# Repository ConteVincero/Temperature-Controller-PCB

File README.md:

# Temperature-Controller
PCB to control the temperature in the house

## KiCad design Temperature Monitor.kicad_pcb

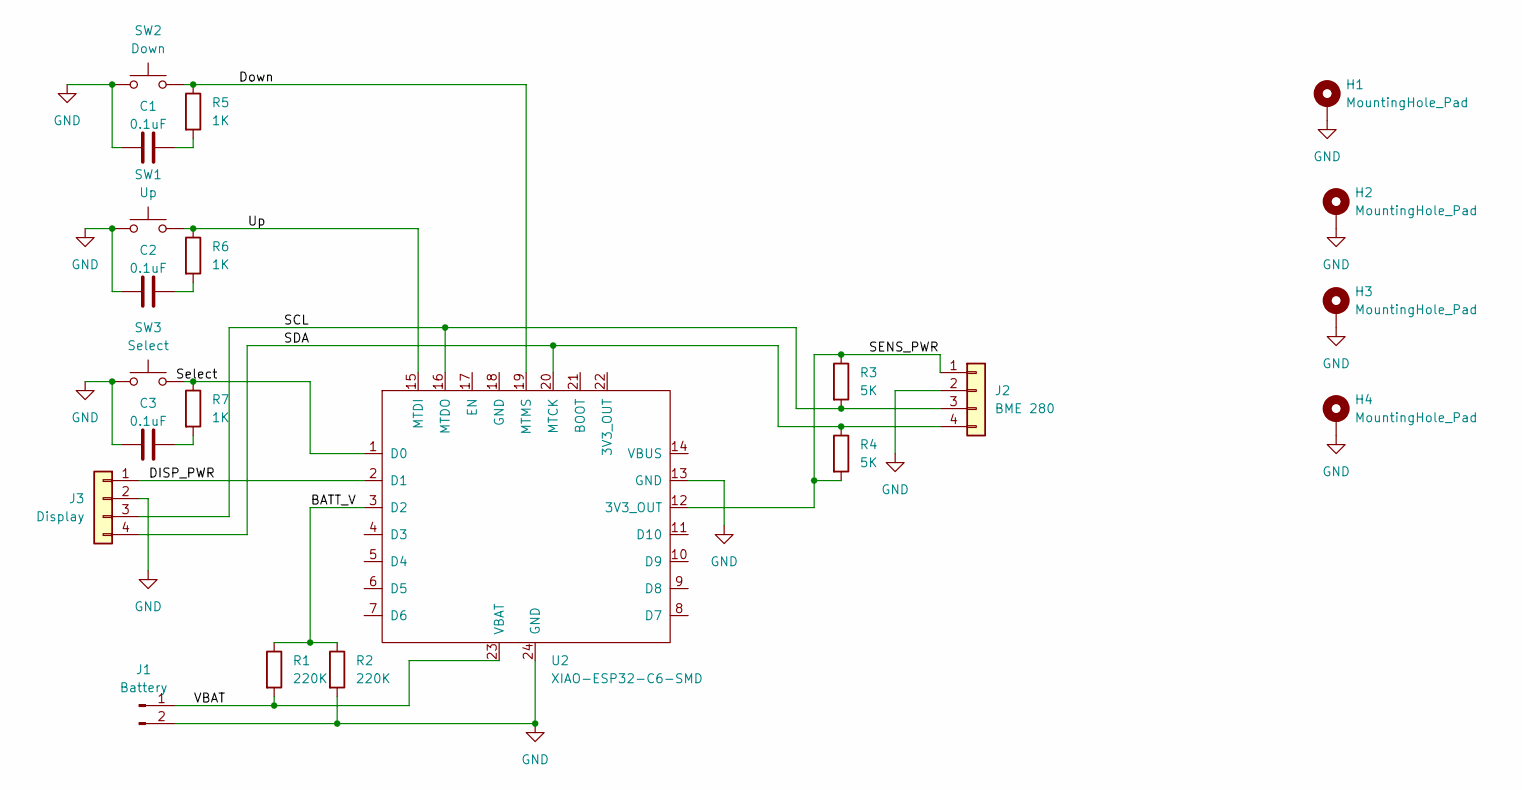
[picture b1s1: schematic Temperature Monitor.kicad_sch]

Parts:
C1, C2, C3: 0.1uF; CP_Radial_D5.0mm_P2.50mm
H1, H2, H3, H4: MountingHole_Pad; MountingHole_3.2mm_M3_ISO7380_Pad_TopBottom
J1: Battery; JST_PH_S2B-PH-K_1x02_P2.00mm_Horizontal
J2: BME 280; PinSocket_1x04_P2.54mm_Vertical
J3: Display; PinSocket_1x04_P2.54mm_Vertical
R1, R2: 220K; R_Axial_DIN0207_L6.3mm_D2.5mm_P7.62mm_Horizontal
R3, R4: 5K; R_Axial_DIN0207_L6.3mm_D2.5mm_P7.62mm_Horizontal
R5, R6, R7: 1K; R_Axial_DIN0207_L6.3mm_D2.5mm_P7.62mm_Horizontal
SW1: Up; SW_TH_Tactile_Omron_B3F-100x
SW2: Down; SW_TH_Tactile_Omron_B3F-102x
SW3: Select; SW_TH_Tactile_Omron_B3F-106x
U2: XIAO-ESP32-C6-SMD

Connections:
/BATT_V: R1.1, R2.1, U2.3 (D2)
/DISP_PWR: J3.1, U2.2 (D1)
/Down: R5.1, SW2.2, U2.19 (MTMS)
/SCL: J2.3, J3.3, R3.2, U2.16 (MTDO)
/SDA: J2.4, J3.4, R4.1, U2.20 (MTCK)
/SENS_PWR: J2.1, R3.1, R4.2, U2.12 (3V3_OUT)
/Up: R6.1, SW1.2, U2.15 (MTDI)
/VBAT: J1.1, R1.2, U2.23 (VBAT)
GND: C1.1, C2.1, C3.1, H1.1 (1_1), H2.1 (1_1), H3.1 (1_1), H4.1 (1_1), J1.2, J2.2, J3.2, R2.2, SW1.1, SW2.1, SW3.1, U2.13 (GND), U2.24 (GND)
unnamed: C1.2, R5.2
unnamed: C2.2, R6.2
unnamed: C3.2, R7.2
unnamed: R7.1, SW3.2, U2.1 (D0)

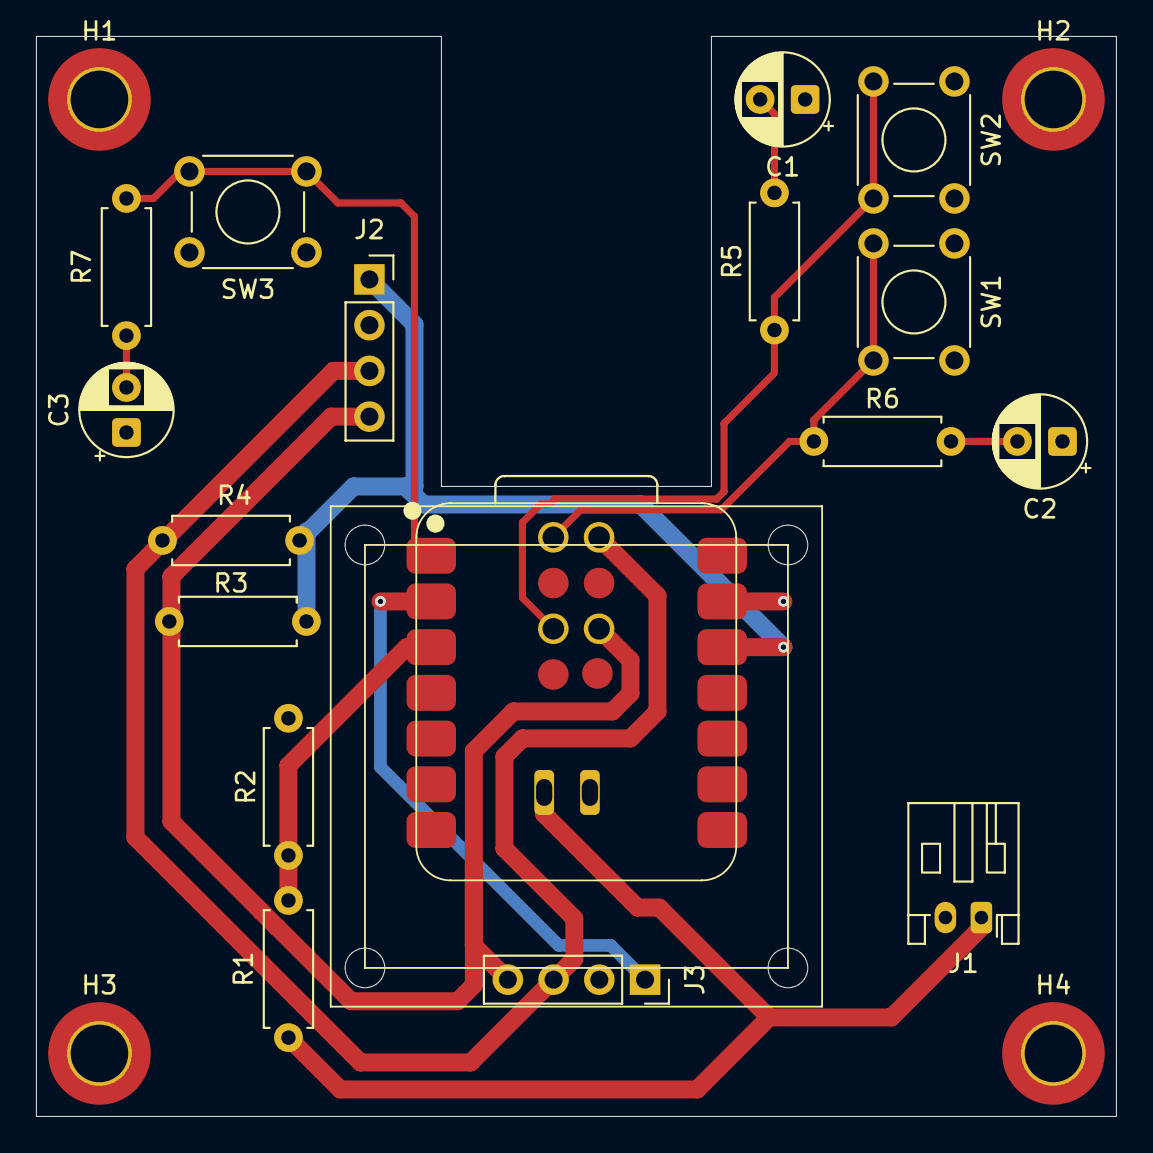
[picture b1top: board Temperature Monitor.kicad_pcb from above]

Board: 2 copper layers, 60.0 x 60.0 mm, 25 parts (0 on the bottom side), 13 nets.

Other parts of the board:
ScreenMount1, ScreenMount2, ScreenMount3, ScreenMount4: MountingHole_2.2mm_M2
